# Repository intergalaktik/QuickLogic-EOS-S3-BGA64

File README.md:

# QuickLogic-EOS-S3-BGA64

## Pinout sorted by BGA pins

Signal Name|Signal Type|I/O Bank|WCLSP Ball|BGA Ball|QFNc|Description|Alternate Function
--|--|--|--|--|--|--|--
IO_2|IO|VCCIOA|--|A1|6||FBIO_2, SPI_SENSOR_SSn2, DEBUG_MON_0, BATT_MON, SENSOR_INT_1 
IO_3|IO|VCCIOA|C7|A2|2||FBIO_3, SENSOR_INT_0 
IO_7|IO|VCCIOA|--|A3|63||FBIO_7, SPI_SENSOR_SSn5, DEBUG_MON_4, SWV, SENSOR_INT_4 
IO_7|IO|VCCIOA|--|A3|63||FBIO_7, SPI_SENSOR_SSn5, DEBUG_MON_4, SWV, SENSOR_INT_4 
IO_10|IO|VCCIOA|B5|A4|59||FBIO_10, SPI_SENSOR_CLK, SWV, SENSOR_INT_4, I2S_DIN, PDM_DIN 
IO_14|IO|VCCIOA|A4|A5|54||FBIO_14, SW_DP_CLK, IrDA_SIROUT, SCL_1, GPIO(3), UART_RXD, SENSOR_INT_5 
LDO_VIN|POWER||B3|A6|50,52|Internal LDO Power Input |
ADC0|ANALOG|ANALOG|B2|A7|48|ADC 0 Input |
AGND|ANA||C3|A8|43|Analog Ground|
IO_0|IO|VCCIOA|A7|B1|4||FBIO_0a, SCL_0 
IO_4|IO|VCCIOA|--|B2|3||FBIO_4, SPI_SENSOR_SSn3, DEBUG_MON_1, SDA_1_DPU, SENSOR_INT_2 
IO_6|IO|VCCIOA|A6|B3|62||FBIO_6, SPI_SENSOR_MOSI, DEBUG_MON_3, FCLK, GPIO(0)b, IrDA_SIRIN, SENSOR_INT_1 
IO_9|IO|VCCIOA|A5|B4|60||FBIO_9, SPI_SENSOR_SSn1, I2S_WD_CLK_O, GPIO(1),PDM_STAT_I, SENSOR_INT_3 
IO_12|IO|VCCIOA|--|B5|56||FBIO_12, SPI_SENSOR_SSn7, DEBUG_MON_6, IrDA_SIROUT, SENSOR_INT_6 
VDD2|POWER||A3|B6|51|LDO 2 Output|
VDD1|POWER||A2|B7|49|LDO 1 Output|
XTAL_IN|ANALOG|ANALOG|A1|B8|44|32 kHz Crystal|32 kHz Clock Input 
IO_1|IO|VCCIOA|B7|C1|5||FBIO_1, SDA_0 
VCCIOA|POWER||C6|C2|1, 58|Bank A VCC In|
IO_5|IO|VCCIOA|--|C3|64||FBIO_5, SPI_SENSOR_SSn4, DEBUG_MON_2, SDA_0_DPU, SENSOR_INT_3
IO_8|IO|VCCIOA|B6|C4|61||FBIO_8, PDM_CLK_O, I2S_CLK_O, IrDA_SIROUT, SENSOR_INT_2 
IO_11|IO|VCCIOA|--|C5|57||FBIO_11, SPI_SENSOR_SSn6, DEBUG_MON_5, GPIO(2), SENSOR_INT_5 
IO_15|IO|VCCIOA|B4|C6|53||FBIO_15, SW_DP_IO, IrDA_SIRIN, SDA_1, UART_TXD, SENSOR_INT_6 
ADC1|ANALOG|ANALOG|--|C7|47|ADC 1 Input |
XTAL_OUT|ANALOG|ANALOG|B1|C8|45|32 kHz Crystal |
IO_43|IO|VCCIOB|D7|D1|7||FBIO_43, AP_INTERRUPT IO_44 IO VCCIOB E7 E1 8 FB
IO_40|IO|VCCIOB|--|D2|13||SPI_MASTER_SSn1, FBIO_40, SCL_2, DEBUG_MON_5, IrDA_SIRIN, SENSOR_INT_3
GND|GND||C4,C5|D3,D4,D5|GND|Ground |
IO_13|IO|VCCIOA|--|D6|55||FBIO_13, SPI_SENSOR_SSn8, DEBUG_MON_7, SWV, SENSOR_INT_7 
IO_17|IO|VCCIOB|D1|D7|42||FBIO_17, SPI_SLAVE_MISO, UART_CTS
AVDD|ANA||C2|D8|46|Analog Power |
IO_44|IO|VCCIOB|E7|E1|8||FBIO_44, SW_DP_IO, SDA_1, UART_TXD, IrDA_SIRIN, SENSOR_INT_4 
IO_38|IO|VCCIOB|E6|E2|16||SPI_MASTER_MOSI, FBIO_38, DEBUG_MON_3, GPIO(6), AP_PDM_CLK_IN, SENSOR_INT_2 
IO_33|IO|VCCIOB|--|E3|21||FBIO_33, SPI_SENSOR_SSn6, DEBUG_MON_7, SCL_1, SENSOR_INT_7
VCCIOB|POWER||D6|E4,E6|12, 24, 35|Bank B VCC In|
STM|INPUT|VCCIOB|D4|E5|29|Connect to ground|
IO_16|IO|VCCIOB|E1|E7|40||FBIO_16, SPI_SLAVE_CLK, UART_RXD 
IO_18|IO|VCCIOB|--|E8|38||FBIO_18, SWV, DEBUG_MON_0, GPIO(4), SENSOR_INT_1 
IO_41|IO|VCCIOB|--|F1|14||FBIO_41, SDA_2, DEBUG_MON_6, IrDA_SIROUT, SENSOR_INT_6
IO_35|IO|VCCIOB|--|F2|18||FBIO_35, SPI_MASTER_SSn3, SPI_SENSOR_SSn7, DEBUG_MON_1, SENSOR_INT_1 
IO_34|IO|VCCIOB|D5|F3|20||SPI_MASTER_CLK, FBIO_34, DEBUG_MON_0, AP_PDM_STAT_O, SENSOR_INT_7 
IO_30|IO|VCCIOB|F4|F4|25||FBIO_30, SPI_SENSOR_SSn1, GPIO(3), I2S_WD_CLK_O, PDM_STAT_I, SENSOR_INT_5 
IO_29|IO|VCCIOB|E3|F5|26||FBIO_29, SPI_SENSOR_MISO, I2S_CLK_O, PDM_CLK_O, IrDA_SIROUT, SENSOR_INT_4 
IO_26|IO|VCCIOB|--|F6|30||FBIO_26, SPI_SENSOR_SSn3, DEBUG_MON_3, GPIO(1), SENSOR_INT_4 
IO_25|IO|VCCIOB|D3|F7|31||FBIO_25, SPI_MASTER_SSn3, SWV, IrDA_SIROUT, UART_RXD, SENSOR_INT_2 
SYS_RSTn|INPUT|VCCIOB|F1|F8|41|System Reset Input|
IO_45|IO|VCCIOB|F7|G1|9||FBIO_45, SW_DP_CLK, SCL_1, UART_RXD, IrDA_SIROUT, GPIO(7), SENSOR_INT_5
IO_37|IO|VCCIOB|--|G2|15||FBIO_37, SPI_SENSOR_SSn8, DEBUG_MON_2, SDA_2_DPU, SENSOR_INT_2 
FSOURCE|VPP||E5|G3|19|Connect to ground |
IO_31|IO|VCCIOB|E4|G4|23||FBIO_31, SPI_SENSOR_CLK, GPIO(4), AP_I2S_CLK_IN, SENSOR_INT_6 
IO_28|IO|VCCIOB|F3|G5|27||FBIO_28, SPI_SENSOR_MOSI, DEBUG_MON_5, GPIO(2), I2S_DIN, PDM_DIN, IrDA_SIRIN, SENSOR_INT_3
IO_24|IO|VCCIOB|D2|G6|32||FBIO_24, AP_I2S_DOUT, IrDA_SIRIN, GPIO(0)b, UART_TXD, SENSOR_INT_1 
IO_22|IO|VCCIOB|--|G7|34||FBIO_22, DEBUG_MON_2, IrDA_SIROUT, GPIO(6), UART_CTS, SENSOR_INT_3
IO_20|IO|VCCIOB|F2|G8|37||FBIO_20, SPI_SLAVE_SSn, UART_TXD IO_21 IO VCCIOB -- H7 39 FB
IO_42|IO|VCCIOB|--|H1|10||FBIO_42, SDA_1_DPU, DEBUG_MON_7, SWV, SENSOR_INT_7
IO_39|IO|VCCIOB|F6|H2|11||FBIO_39, DEBUG_MON_4, AP_PDM_IO, SENSOR_INT_3 
IO_36|IO|VCCIOB|F5|H3|17||SPI_MASTER_MISO, FBIO_36, SWV, SPI_SENSOR_SSn2, GPIO(5), SENSOR_INT_1 
IO_32|IO|VCCIOB|--|H4|22||FBIO_32, SPI_SENSOR_SSn5, DEBUG_MON_6, SDA_1, SENSOR_INT_6
IO_27|IO|VCCIOB|--|H5|28||FBIO_27, SPI_MASTER_SSn2, SPI_SENSOR_SSn4, DEBUG_MON_4, SENSOR_INT_5 
IO_23|IO|VCCIOB|E2|H6|33||FBIO_23, SPI_MASTER_SSn2, SWV, GPIO(7), AP_I2S_WD_CLK_IN, SENSOR_INT_7 
IO_21|IO|VCCIOB|--|H7|39||FBIO_21, DEBUG_MON_1, IrDA_SIRIN, GPIO(5), UART_RTS, SENSOR_INT_2 
IO_19|IO|VCCIOB|C1|H8|36||FBIO_19, SPI_SLAVE_MOSI, UART_RTS Note: IO_19 can serve as bootstrap for debugger mode as an M4-F reset release mechanism. 

Symbol library taken from: QuickFeather Development Board

https://github.com/QuickLogic-Corp/quick-feather-dev-board

Revorked to BGA64 by Intergalaktik

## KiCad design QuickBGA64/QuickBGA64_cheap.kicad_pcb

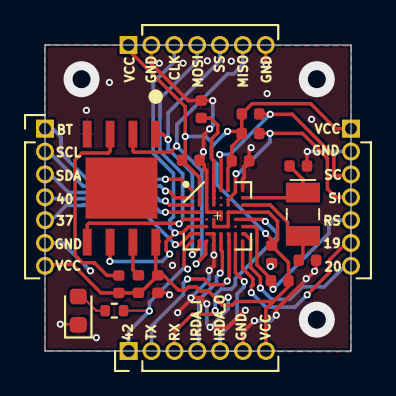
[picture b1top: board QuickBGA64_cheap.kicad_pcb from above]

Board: 2 copper layers, 17.0 x 17.0 mm, 21 parts (0 on the bottom side), 27 nets.

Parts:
C1, C2: 12pF; C_0402_1005Metric
C3, C4, C5, C6: 100n; C_0402_1005Metric
D1: LED; LED_0603_1608Metric
IC1: EOS-S3-BGA64; BGA-64_3.5x3.5mm_Layout8x8_P0.4mm_cheap
J1: TOP; PinHeader_1x07_P1.27mm_Vertical
J2: RIGHT; PinHeader_1x07_P1.27mm_Vertical
J3: BOTTOM; PinHeader_1x07_P1.27mm_Vertical
J4: LEFT; PinHeader_1x07_P1.27mm_Vertical
R1, R2, R3, R4, R5, R6: 10K; R_0402_1005Metric
R7: R300; R_0402_1005Metric
U1: GD25Q16CWIGR; GD25Q16CWIG
Y1: ECS-_327-12_5-34B-TR; SMD-2_3.2x1.5mm

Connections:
/37: IC1.G2, J4.5
/40: IC1.D1, IC1.D2, J4.4
/42: IC1.H1, J3.1, R7.2
/BAT_M: IC1.A1, J4.1
/B_19: IC1.H8, J2.6
/B_20: IC1.G8, J2.7
/CLK: IC1.F1, IC1.F2, IC1.F3, J1.3, U1.6
/HS_OSC_9: IC1.A4, IC1.B4, IC1.C4, R4.1
/IrDA_I: IC1.G5, IC1.H5, J3.4
/IrDA_O: IC1.G7, IC1.H7, J3.5
/MISO: IC1.H3, J1.6, U1.2
/MOSI: IC1.E2, J1.4, U1.5
/RST: IC1.F8, J2.5, R1.2
/RX: IC1.E7, IC1.E8, J3.3
/SCL: IC1.B1, J4.2
/SDA: IC1.C1, J4.3
/SS: IC1.H2, J1.5, U1.1
/SWD_CLK: IC1.A5, J2.3, R6.2
/SWD_IO: IC1.A7, IC1.C6, J2.4, R5.2
/TX: IC1.G6, IC1.H6, J3.2
/X0: C2.1, IC1.C8, Y1.2
/X1: C1.1, IC1.B8, Y1.1
GND: C1.2, C2.2, C3.1, C4.1, C5.1, C6.1, D1.1, IC1.A3, IC1.A8, IC1.B3, IC1.C3, IC1.D3, IC1.D4, IC1.D5, IC1.E5, IC1.G3, IC1.G4, IC1.H4, J1.2, J1.7, J2.2, J3.6, J4.6, R4.2, U1.4
unnamed: D1.2, R7.1
unnamed: R2.2, U1.7
unnamed: R3.2, U1.3
VCC: C3.2, C4.2, C5.2, C6.2, IC1.A2, IC1.A6, IC1.B2, IC1.C2, IC1.D6, IC1.D8, IC1.E4, IC1.E6, IC1.F4, IC1.F5, IC1.F6, J1.1, J2.1, J3.7, J4.7, R1.1, R2.1, R3.1, R5.1, R6.1, U1.8

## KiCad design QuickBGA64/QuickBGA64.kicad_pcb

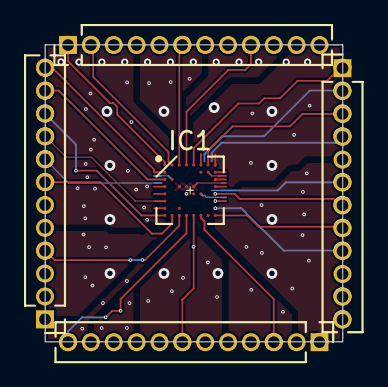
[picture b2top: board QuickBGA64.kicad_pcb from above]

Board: 4 copper layers, 16.5 x 16.5 mm, 5 parts (0 on the bottom side), 21 nets.

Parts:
IC1: EOS-S3-BGA64; BGA-64_3.5x3.5mm_Layout8x8_P0.4mm_cheap
J1: TOP; PinHeader_1x12_P1.27mm_Vertical
J2: RIGHT; PinHeader_1x12_P1.27mm_Vertical
J3: BOTOM; PinHeader_1x12_P1.27mm_Vertical
J4: LEFT; PinHeader_1x12_P1.27mm_Vertical

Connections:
/2: IC1.A1, J1.1
/3: IC1.A2, J1.2
/7: IC1.A3, J1.6
/10: IC1.A4, J1.9
/14: IC1.A5, J2.1
/18: IC1.E8, J2.7
/19: IC1.H8, J2.8
/20: IC1.G8, J2.9
/21: IC1.H7, J2.10
/23: IC1.H6, J3.3
/27: IC1.H5, J3.7
/32: IC1.H4, J3.12
/36: IC1.H3, J4.4
/39: IC1.H2, J4.7
/41: IC1.F1, J4.9
/42: IC1.H1, J4.10
/A0: IC1.A7, J2.3
/SCL: IC1.B1, J4.12
/SDA: IC1.C1, J4.11
GND: IC1.A8, IC1.D3, IC1.D4, IC1.D5, J2.12, J3.1
VCC: IC1.A6, IC1.B6, IC1.B7, IC1.C2, IC1.D8, IC1.E4, IC1.E6, J2.11

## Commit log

2020-10-01 Adding initial footprint
2020-10-01 Adding initial pinout table
2020-10-02 Changing pad sie to 0.25mm
2020-10-02 Adding symbol library
2020-10-02 Symbol update
2020-10-02 Adding schematics and pcb
2020-10-08 Adding Cheap option
2020-11-05 Adding LED, sending to production
